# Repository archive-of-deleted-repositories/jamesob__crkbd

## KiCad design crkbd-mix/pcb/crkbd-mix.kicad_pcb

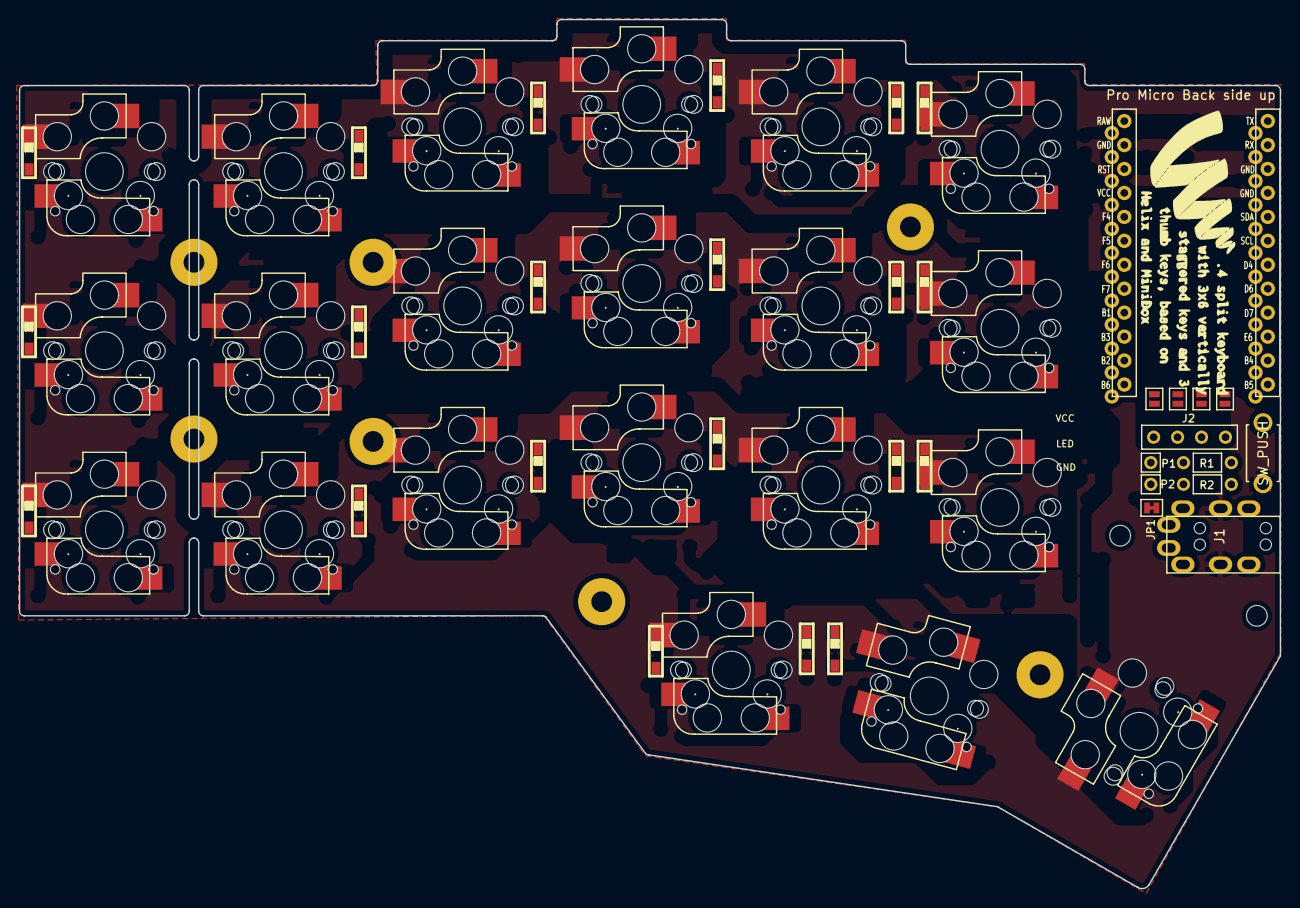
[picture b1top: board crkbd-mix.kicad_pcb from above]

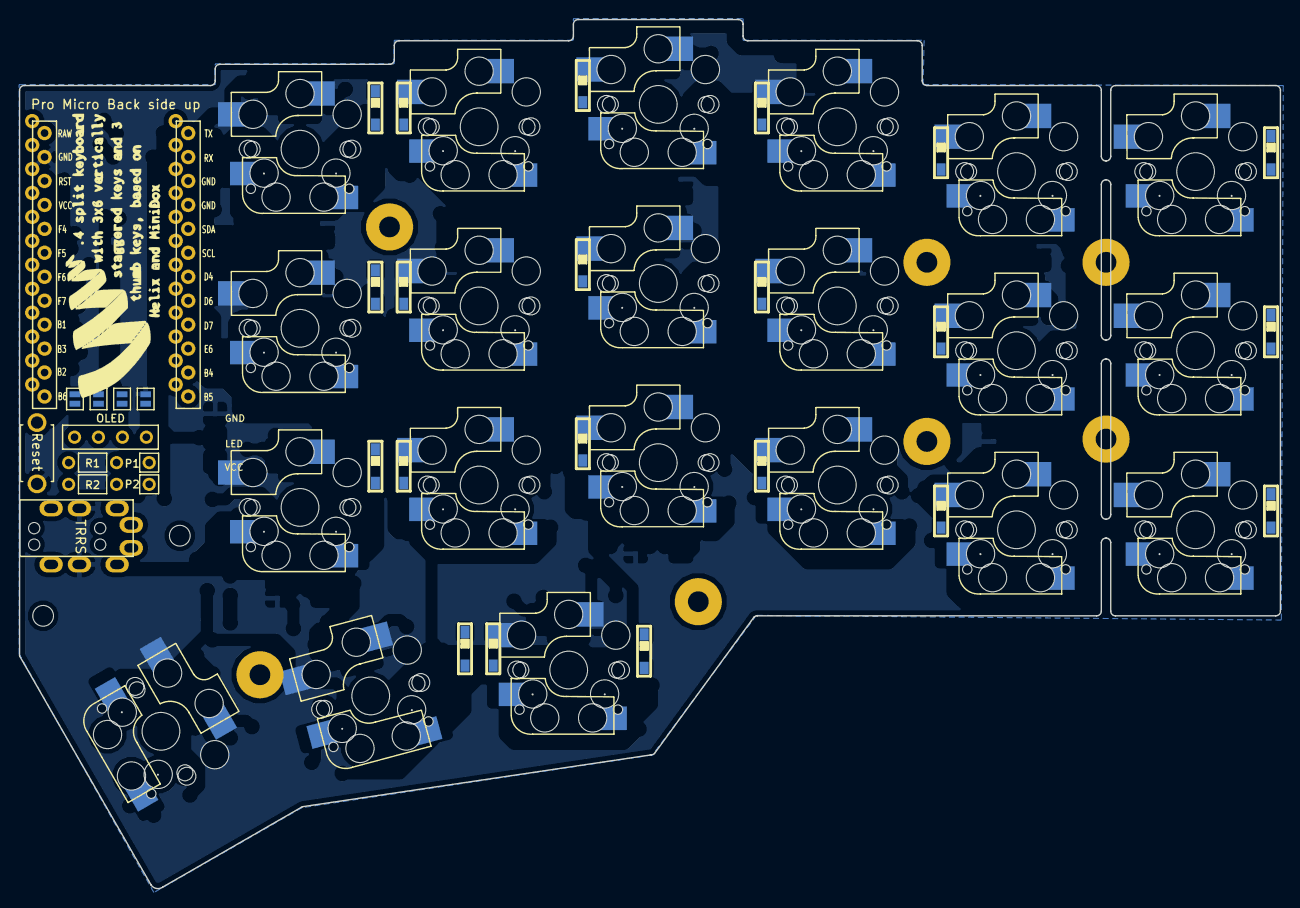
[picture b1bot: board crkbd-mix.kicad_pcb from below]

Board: 2 copper layers, 133.8 x 92.2 mm, 59 parts (4 on the bottom side), 43 nets, no tracks yet.

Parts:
D1, D2, D3, D4, D5, D6, D7, D8, D9, D10, D11, D12, D13, D14, D15, D16, D17, D18, D19, D20, D21: D; D3_SMD
J1: MJ-4PP-9
J2: OLED
JP1: JPC2
JP2, JP3, JP4, JP5, JP6, JP7, JP8, JP9: Jumper
P1, P2: i2c-pin; 1pin_conn
R1, R2: R
RSW1: SW_PUSH; ResetSW
SW1, SW2, SW3, SW4, SW5, SW6, SW7, SW8, SW9, SW10, SW11, SW12, SW13, SW14, SW15, SW16, SW17, SW18, SW19, SW20, SW21: SW_PUSH; CherryMX_KailhLowProfile_Hotswap
U1: ProMicro; ProMicro_v2

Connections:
GND: J1.C, JP2.1, JP9.1, RSW1.2, U1.3, U1.4, U1.23
unnamed: D1.2, SW1.2
unnamed: D2.2, SW2.2
unnamed: D3.2, SW3.2
unnamed: D4.2, SW4.2
unnamed: D5.2, SW5.2
unnamed: D6.2, SW6.2
unnamed: D7.2, SW7.2
unnamed: D8.2, SW8.2
unnamed: D9.2, SW9.2
unnamed: D10.2, SW10.2
unnamed: D11.2, SW11.2
unnamed: D12.2, SW12.2
unnamed: D13.2, SW13.2
unnamed: D14.2, SW14.2
unnamed: D15.2, SW15.2
unnamed: D16.2, SW16.2
unnamed: D17.2, SW17.2
unnamed: D18.2, SW18.2
unnamed: D19.2, SW19.2
unnamed: D20.2, SW20.2
unnamed: D21.2, SW21.2
unnamed: J1.A, P1.1
unnamed: J1.B, JP1.2, P2.1
unnamed: J2.1, JP5.2, JP9.2
unnamed: J2.2, JP4.2, JP8.2
unnamed: J2.3, JP3.2, JP7.2
unnamed: J2.4, JP2.2, JP6.2
SCL: JP4.1, JP7.1, R2.2, U1.6
SDA: JP5.1, JP6.1, R1.2, U1.5
VCC: J1.D, JP3.1, JP8.1, R1.1, R2.1, U1.21
col0: SW1.1, SW7.1, SW13.1, U1.20
col1: SW2.1, SW8.1, SW14.1, U1.19
col2: SW3.1, SW9.1, SW15.1, U1.18
col3: SW4.1, SW10.1, SW16.1, SW19.1, U1.17
col4: SW5.1, SW11.1, SW17.1, SW20.1, U1.16
col5: SW6.1, SW12.1, SW18.1, SW21.1, U1.15
data: JP1.1, U1.2
reset: RSW1.1, U1.22
row0: D1.1, D2.1, D3.1, D4.1, D5.1, D6.1, U1.7
row1: D7.1, D8.1, D9.1, D10.1, D11.1, D12.1, U1.8
row2: D13.1, D14.1, D15.1, D16.1, D17.1, D18.1, U1.9
row3: D19.1, D20.1, D21.1, U1.10

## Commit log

2018-05-26 Update LICENSE
    update format.
2018-05-28 Export case data
2018-06-03 Update frames of case
2018-06-03 Add build guide
2018-06-09 Resize hole and replace lines
2018-06-12 Add procedure of promicro soket
2018-06-20 Update holes of switches
2018-06-21 Update case files
2018-06-25 Update case holes
2018-08-02 Update photos
2018-08-02 Add new lineups
2018-08-10 Rename crkbd++ to crkbd-mix
2018-08-10 Replace footprints for double hotswapable
2018-08-21 Add dxf files
2018-08-24 remove unused projects
2018-08-24 Rename crkbd to corne classic and some fix
2018-08-24 Rewrite case files by illustrator
2018-08-24 Setup corne cherry
2018-08-25 Update case data and add tent data
2018-08-31 Update LED foot prints
2018-08-31 Update corne-cherry
2018-08-31 Fix plate directories
2018-08-31 Remove script
2018-08-31 Setup prot
2018-09-12 Update refs in pcbnew
2018-09-22 Some fix
2018-09-22 Remove info
2018-09-22 Add a thumb key
2018-10-06 Add doc page for corne-cherry
2018-10-13 Move LICENSE file
2018-10-13 Update LICENSE
2018-10-13 Remove corne-cherry and update README
2018-10-18 Publish corne-cherry
2018-10-18 Add LICENSE
2018-11-14 Update switch hole size and gnd pattern
2018-11-15 Fix version
2018-11-16 Copy cherry to chocolate
2018-12-09 typo fix for corne-classic/doc/buildguide_jp.md
2018-12-09 Remove unnecessary files
2018-12-09 Update top-plate
2018-12-09 Clean common files
2018-12-09 Update holes
2018-12-11 Add English version of corne-classic build-guide
2018-12-31 ignore gerber
2018-12-31 Some updates
2018-12-31 Rename
2018-12-31 Remove unused file
2018-12-31 Fix acrylic plate size
2018-12-31 Add corne-light
2019-02-10 Update tent plate
2019-02-10 Rename acrylic_plates
2019-02-10 Update buildguides
2019-02-10 Update lines
2019-02-15 Brashup righ hand
2019-02-19 Add tilting tenting doc
2019-02-19 Update light
2019-02-19 Update cherry
2019-02-22 Update buildguide_tilting_tenting_plate_jp.md
    非対応分を明確に修正
2019-10-02 Move acrylic_plate
2019-10-02 Update acrylic_plates
2019-10-02 Add plate for mini
2019-10-10 Added info on SMD diode polarity to english build guide.
2019-10-10 Improved LED soldering section of english build guide.
    Adds some extra info on how to orient the LEDs, how you can go about soldering
    them and a warning that LEDs need to be turned on in the default firmware to
    actually light up.
2019-10-10 Added clearer ProMicro orientation instructions to the english build guide.
2019-10-10 Added more info on testing to the english builde guide.
2019-10-10 Added info on how to turn LEDs on to the firmware section of the english build guide.
2019-11-04 corne-light-rev1.1.0
2019-11-20 Update configs
2019-11-26 Add build-guide for corne-light
2019-11-26 Add top-plate for light
2019-11-26 Add corne-light photos in README.md
2019-12-13 fixed typo
2019-12-29 Fix typo in #define name
2020-02-11 Add cherry+ top-middle plate
2020-02-11 Move case/acrylic_plate to plates
2020-02-11 Update directory tree
2020-04-13 Add kailh low profiile
2020-05-19 Add tenting mini crkbrd version
2020-06-26 remove cache files
    see http://kicad-pcb.org/help/file-formats/
    > fp-info-cache: *: Footprint info cache:
    cache of information (description, datasheet URL, etc.)
    for all footprints used by the board.
2020-06-26 gitignore: simplify _gerber_ dir exclusion
    gitignore globs are not repo-global by default.
    They are so only with an explicit `/` in front.
    Also, all files below an ignored directory
    are ignored as well.
2020-06-26 git ignore more files created by KiCAD (& co.)
2020-07-06 Added a troubleshoot section to the english build guide.
2020-07-07 Improve Corne Chocolate EN build-guide (was google-translated)
    Apart form language, it also fixes formatting, so some links,
    images and code-blocks are now shown as they should.
2020-07-07 README: Adds links to the build guides
2020-07-29 Only link language shortcuts and put JP before EN
    This is applying suggestions from code review by @foostan
2020-08-04 Update cuts and footprints
2020-08-04 Update footprints
2020-08-08 Add release gerber files GitHub Actions workflow
2020-09-05 Add release flows for each products
2020-09-05 Update pcb plates
2020-09-05 Update acrylic plates
2020-09-05 Add acrylic plate data with release
2020-09-05 Cleanup
2020-09-05 Add git-submodule
2020-09-05 Update lib tables
2020-09-05 Add Makefile
